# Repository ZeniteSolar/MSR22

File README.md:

# MSR22
Módulo para comunicação serial I2C e USART com duas entradas para leituras analógicas.

Com dois acessos ao barramento I2C e um para USART este módulo foi projetado para os sensores MPU6050 e o módulo GPS Ublox M8N.

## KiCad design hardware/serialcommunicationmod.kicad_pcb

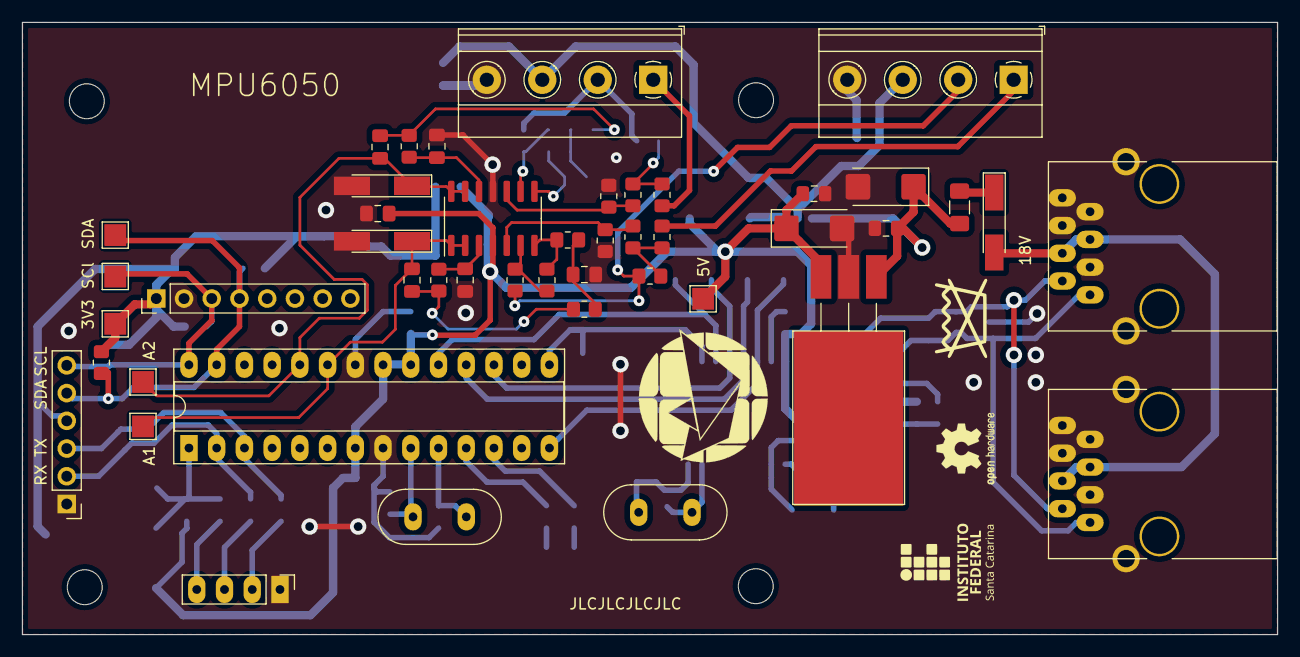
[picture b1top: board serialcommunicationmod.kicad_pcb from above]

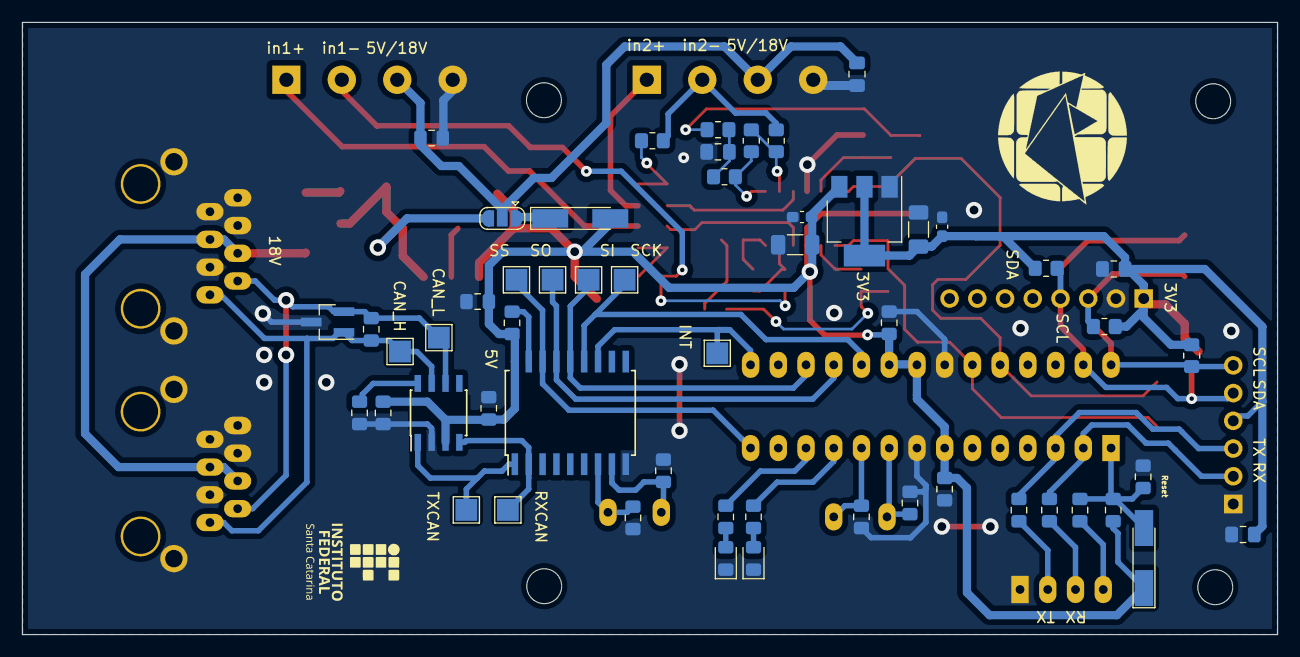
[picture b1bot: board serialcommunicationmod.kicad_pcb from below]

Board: 2 copper layers, 115.0 x 56.1 mm, 110 parts (56 on the bottom side), 55 nets.

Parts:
C4, C5, C6, C7, C8, C9, C374: 100n; C_0805_2012Metric_Pad1.18x1.45mm_HandSolder
C101, C103, C104: 100nF; C_0805_2012Metric_Pad1.18x1.45mm_HandSolder
C102, C201, C202, C205, C401, C402, C405, C406, C502, C503: 100nF; C_0805_2012Metric_Pad1.15x1.40mm_HandSolder
C203, C204, C403, C404: 22pF; C_0805_2012Metric_Pad1.15x1.40mm_HandSolder
C407, C410: 1u; C_1206_3216Metric_Pad1.33x1.80mm_HandSolder
C408, C409: 100n; C_0603_1608Metric_Pad1.08x0.95mm_HandSolder
C501, C504: 1uF; CP_EIA-6032-20_AVX-F_Pad2.25x2.35mm_HandSolder
D2, D3: 4V7; D_MiniMELF_Handsoldering
D101, D401, D501: LL4148; D_MiniMELF_Handsoldering
D201: D_TVS_Dual_AAC; SOT-23_Handsoldering
D402: LED2; LED_0805_2012Metric_Pad1.15x1.40mm_HandSolder
D403: LED1; LED_0805_2012Metric_Pad1.15x1.40mm_HandSolder
F501: 500mA; Fuse_1206_3216Metric_Pad1.42x1.75mm_HandSolder
H101, H102, H103, H104: MountingHole; MountingHole_3.2mm_M3
J101, J102: SENSOR; TerminalBlock_Phoenix_MKDS-1,5-4-5.08_1x04_P5.08mm_Horizont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
J103: Conn_01x08; PinHeader_1x08_P2.54mm_Vertical
J104: Conn_01x06; PinHeader_1x06_P2.54mm_Vertical
J401: USART; PinHeader_1x04_P2.54mm_Vertical
J601, J602: RJ45; RJ45_YH59_01
JP101: jmp; SolderJumper-3_P1.3mm_Open_RoundedPad1.0x1.5mm
LOGO101: Logo_Open_Hardware_Small; OSHW-Logo2_7.3x6mm_SilkScreen
R4, R5, R6, R7, R8, R9, R27, R28, R30, R32, R34, R35, R37, R38, R43, R44, R45, R46: 1k; R_0805_2012Metric_Pad1.20x1.40mm_HandSolder
R101, R102, R103, R104: 10k; R_0805_2012Metric_Pad1.20x1.40mm_HandSolder
R201: 120; R_0805_2012Metric_Pad1.15x1.40mm_HandSolder
R202: 4k7; R_0805_2012Metric_Pad1.15x1.40mm_HandSolder
R203, R401: 10k; R_0805_2012Metric_Pad1.15x1.40mm_HandSolder
R402, R403, R404, R405: 1k; R_0805_2012Metric_Pad1.15x1.40mm_HandSolder
SYM101, SYM102: SYM_Radioactive_Radiation_Small; symbol_logoZenite
SYM103: SYM_Radioactive_Radiation_Small; symbol_naolavar
SYM104, SYM105: SYM_LASER_Small; synbol_logoifsc
TP101: 5V; TestPoint_Pad_2.0x2.0mm
TP102: 3V3; TestPoint_Pad_2.0x2.0mm
TP201: SI; TestPoint_Pad_2.0x2.0mm
TP202: SO; TestPoint_Pad_2.0x2.0mm
TP203: TXCAN; TestPoint_Pad_2.0x2.0mm
TP204: RXCAN; TestPoint_Pad_2.0x2.0mm
TP205: SC; TestPoint_Pad_2.0x2.0mm
TP206: SCK; TestPoint_Pad_2.0x2.0mm
TP207: CAN_H; TestPoint_Pad_2.0x2.0mm
TP208: CAN_L; TestPoint_Pad_2.0x2.0mm
TP209: INT; TestPoint_Pad_2.0x2.0mm
TP210, TP211: TestPoint_Pad_2.0x2.0mm
TP601: SDA; TestPoint_Pad_2.0x2.0mm
TP602: SCL; TestPoint_Pad_2.0x2.0mm
U201: MCP2551-I/SN; SOIC-8_3.9x4.9mm_P1.27mm
U202: MCP2515-xSO; SOIC-18W_7.5x11.6mm_P1.27mm
U301: LM324; SOIC-14_3.9x8.7mm_P1.27mm
U302: DIP-28_W7.62mm_Socket_LongPads
U401: AMS1117-3.3; SOT-223-3_TabPin2
U501: LM7805; TO-220-3_Horizontal_TabDown_SMD
Y201, Y401: 16MHz; Crystal_HC49-U_Vertical

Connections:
+3V3: C103.1, C104.1, C409.2, C410.2, J103.1, J104.4, R101.1, R102.1, R103.1, R104.1, TP102.1, U401.2 (VO)
+5V: C201.1, C202.1, C205.1, C374.1, C401.1, C402.2, C407.2, C408.2, C503.1, C504.1, D101.2 (A), D401.1 (K), R203.1, R401.1, TP101.1, U201.3 (VDD), U202.18 (VDD), U301.4 (V+), U302.7 (VCC), U302.20 (AVCC), U302.21 (AREF), U401.3 (VI), U501.3 (VO)
/CANBUS CONN/CAN_18V: D501.2 (A), J601.4, J601.5, J602.4, J602.5
/CANBUS CONN/CAN_H: D201.1 (A1), J601.1, J602.1, R201.2, TP207.1, U201.7 (CANH)
/CANBUS CONN/CAN_L: D201.2 (A2), J601.2, J602.2, R201.1, TP208.1, U201.6 (CANL)
/CANBUS/RXCAN: TP204.1, U201.4 (RXD), U202.2 (RXCAN)
/CANBUS/TXCAN: TP203.1, U201.1 (TXD), U202.1 (TXCAN)
/MCU/LED1: R405.1, U302.11 (PD5)
/MCU/LED2: R404.1, U302.12 (PD6)
/MCU/MCP_INT: TP209.1, U202.12 (~INT), U302.15 (PB1)
/MCU/MCP_SS: TP205.1, U202.16 (~CS), U302.14 (PB0)
/MCU/RESET: C405.1, C406.2, D401.2 (A), R401.2, U302.1 (~RESET/PC6)
/MCU/analog1: C7.2, D3.1 (K), TP210.1, U301.1, U301.2 (-), U302.23 (PC0)
/MCU/analog2: C6.2, D2.1 (K), TP211.1, U301.13 (-), U301.14, U302.24 (PC1)
/MISO: TP202.1, U202.15 (SO), U302.18 (PB4)
/MOSI: TP201.1, U202.14 (SI), U302.17 (PB3)
/OPAMP/in1+: J102.1, R27.2
/OPAMP/in1-: J102.2, R30.1, R34.1
/OPAMP/in2+: J101.1, R28.2
/OPAMP/in2-: J101.2, R32.1, R37.1
/POWER SUPPLY/+18V_OUT: C501.1, C502.1, F501.2, JP101.3 (B), U501.1 (VI)
/RX: J104.2, R402.1, U302.2 (PD0)
/SCK: TP206.1, U202.13 (SCK), U302.19 (PB5)
/SCL: J103.3, J104.6, R101.2, R103.2, TP602.1, U302.28 (PC5)
/SDA: J103.4, J104.5, R102.2, R104.2, TP601.1, U302.27 (PC4)
/TX: J104.3, R403.1, U302.3 (PD1)
GND: C4.2, C5.2, C8.2, C9.2, C101.2, C102.2, C103.2, C104.2, C201.2, C202.2, C203.2, C204.2, C205.2, C374.2, C401.2, C402.1, C403.2, C404.2, C406.1, C407.1, C408.1, C409.1, C410.1, C501.2, C502.2, C503.2, C504.2, D2.2 (A), D3.2 (A), D201.3 (common), D402.1 (K), D403.1 (K), J101.4, J102.4, J103.2, J104.1, J401.1, J601.3, J601.6, J601.7, J601.8, J601.9 (SH), J602.3, J602.6, J602.7, J602.8, J602.9 (SH), R44.2, R46.2, R202.2, U201.2 (VSS), U202.9 (VSS), U301.11 (V-), U302.8 (GND), U302.22 (GND), U401.1 (GND), U501.2 (GND)
unnamed: C4.1, R4.1, R6.2
unnamed: C5.1, R5.1, R7.2
unnamed: C6.1, R6.1, R8.2
unnamed: C7.1, R7.1, R9.2
unnamed: C8.1, R8.1, U301.12 (+)
unnamed: C9.1, R9.1, U301.3 (+)
unnamed: C101.1, C102.1, J101.3, J102.3, JP101.2 (C)
unnamed: C203.1, U202.7 (OSC2), Y201.1
unnamed: C204.1, U202.8 (OSC1), Y201.2
unnamed: C403.1, U302.10 (XTAL2/PB7), Y401.1
unnamed: C404.1, U302.9 (XTAL1/PB6), Y401.2
unnamed: C405.2, J401.4
unnamed: D101.1 (K), JP101.1 (A)
unnamed: D402.2 (A), R404.2
unnamed: D403.2 (A), R405.2
unnamed: D501.1 (K), F501.1
unnamed: J401.2, R403.2
unnamed: J401.3, R402.2
unnamed: R4.2, R45.2, U301.8
unnamed: R27.1, R30.2, R35.1
unnamed: R28.1, R32.2, R38.1
unnamed: R34.2, R43.1, U301.6 (-)
unnamed: R35.2, R44.1, U301.5 (+)
unnamed: R37.2, R45.1, U301.9 (-)
unnamed: R38.2, R46.1, U301.10 (+)
unnamed: R5.2, R43.2, U301.7
unnamed: R202.1, U201.8 (STBY)
unnamed: R203.2, U202.17 (~RESET)

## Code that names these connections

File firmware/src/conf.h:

/**
 * @file conf.h
 *
 * @defgroup CONF Configurations
 *
 * @brief General configuration of the system.
 *
 */
#ifndef CONF_H
#define CONF_H
#include "../lib/log2.h"

#ifndef F_CPU
#define F_CPU 16000000UL    //define a frequencia do microcontrolador - 16MHz
#endif /* ifndef F_CPU */


// CONFIGURACOES DE COMPILACAO
//#define DEBUG_ON
#define VERBOSE_ON
// #define VERBOSE_ON_CAN_APP
#define VERBOSE_ON_MACHINE
// #define VERBOSE_ON_ADC
#define VERBOSE_ON_INIT
#define VERBOSE_ON_ERROR

// MODULES ACTIVATION
#define USART_ON
#define CAN_ON
//#define CAN_DEPENDENT
#define ADC_ON
#define MACHINE_ON
#define LED_ON
#define WATCHDOG_ON
#define SLEEP_ON
#define PRINT_INFOS

#define CAN_SIGNATURE_SELF                  CAN_SIGNATURE_MSC19_1

#ifdef ADC_ON
// ADC CONFIGURATION
// note that changing ADC_FREQUENCY may cause problems with avg_sum_samples
// #define ADC_8BITS
#define ADC_FREQUENCY                       10000 // 20000
#define ADC_TIMER_PRESCALER                 64
#define ADC_TOP_CTC                         F_CPU/(ADC_TIMER_PRESCALER * 2UL * ADC_FREQUENCY) -1

#if ADC_TOP_CTC >= 256
    #error "Value for ADC timer top is greater than 8 bits"
#elif ADC_TOP_CTC < 2
    #error "Value for ADC timer top is too low, increase the prescaler"
#endif

// #define VSCALE_FACTOR                       10000L  // Scaling to maintain precision, result uint16 for can msg

/** @brief Circular buffer size definitions 
 * Using equal size for adc structures...
 * one could replicate the structure delacartion with different sizes
 * or even, % TODO use dynamic allocation for strucutres 
 */
#define ADC_AVG_SIZE_10                     64
#if (ADC_AVG_SIZE_10 == 0 || (ADC_AVG_SIZE_10 & (ADC_AVG_SIZE_10 - 1)) != 0)
    #error "ADC_AVG_SIZE_10 must be a power of 2!"
#endif
#define cbuf_adc0_SIZE                      ADC_AVG_SIZE_10  /**< Buffer size for ADC0 */
#define cbuf_adc0_SIZE_LOG2                 log2_function(cbuf_adc0_SIZE)   /**< Log2 of buffer size */
#define cbuf_adc1_SIZE                      ADC_AVG_SIZE_10  /**< Buffer size for ADC1 */
#define cbuf_adc1_SIZE_LOG2                 log2_function(cbuf_adc1_SIZE)    /**< Log2 of buffer size */
#endif //ADC_ON



#ifdef MACHINE_ON
// ----> Cbuf used + not a power module ---> no need for even numbers between ADC and Machine frequencies
// no need for clk divider 
#define MACHINE_FREQUENCY                   100           //<! machine timer frequency in Hz
#define MACHINE_TIMER_PRESCALER             1024          //<! machine timer prescaler
#define MACHINE_TOP_CTC                     F_CPU/(MACHINE_TIMER_PRESCALER * 2UL * MACHINE_FREQUENCY) -1
#if MACHINE_TOP_CTC >= 256
    #error "Value for Machine timer top is greater than 8 bits"
#elif MACHINE_TOP_CTC < 2
    #error "Value for Machine timer top is too low, increase the prescaler"
#endif

// The machine frequency may not be superior of ADC_FREQUENCY/ADC_AVG_SIZE_10
#if MACHINE_FREQUENCY > (ADC_FREQUENCY/ADC_AVG_SIZE_10)
    #error "Machine runs faster than the required time to fill the ADC ring buffer"
#endif
#endif // MACHINE_ON

#ifdef LED_ON
#define     LED_PORT                PORTD
#define     LED_PIN                 PIND
#define     LED_DDR                 DDRD
#define     LED1                    PD5
#define     LED2                    PD6
#define     cpl_led(y)              cpl_bit(LED_PORT, y)
#define     set_led(y)              set_bit(LED_PORT, y)
#define     clr_led(y)              clr_bit(LED_PORT, y)
#else
#define     cpl_led()
#define     set_led()
#define     clr_led()
#endif // LED_ON


#ifdef CAN_ON
#define SPI_ON
#define CAN_APP_SEND_STATE_FREQ     10//36000     //<! state msg frequency in Hz
#define CAN_APP_SEND_ADC_FREQ       50//6000      //<! adc msg frequency in Hz
#if MACHINE_FREQUENCY % CAN_APP_SEND_STATE_FREQ != 0
    #warning "CAN_APP_SEND_STATE_FREQ doesn't have a multiple equal to MACHINE_FREQUENCY, this frequency will be truncated"
#endif

#if MACHINE_FREQUENCY % CAN_APP_SEND_ADC_FREQ != 0
    #warning "CAN_APP_SEND_ADC_FREQ doesn't have a multiple equal to MACHINE_FREQUENCY, this frequency will be truncated"
#endif

// CANBUS DEFINITONS
// ----------------------------------------------------------------------------
/* Global settings for building the can-lib and application program.
 *
 * The following two #defines must be set identically for the can-lib and
 * your application program. They control the underlying CAN struct. If the
 * settings disagree, the underlying CAN struct will be broken, with
 * unpredictable results.
 * If can.h detects that any of the #defines is not defined, it will set them
 * to the default values shown here, so it is in your own interest to have a
 * consistent setting. Ommiting the #defines in both can-lib and application
 * program will apply the defaults in a consistent way too.
 *
 * Select if you want to use 29 bit identifiers.
 */
#define	SUPPORT_EXTENDED_CANID	0

/* Select if you want to use timestamps.
 * Timestamps are sourced from a register internal to the AT90CAN.
 * Selecting them on any other controller will have no effect, they will
 * be 0 all the time.
 */
#define	SUPPORT_TIMESTAMPS		0
#endif // CAN_ON

#endif /* ifndef CONF_H */

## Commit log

2022-07-01 hardware: silkscreen updated with JLC. Finished.
2022-09-25 Copy firmware from MVC19, removed ui.*
2022-09-25 remove UI
2022-09-25 Remove oled-display
2022-09-25 Added gps files
2025-03-19 commit inicial do modo voltimetro
2025-03-23 implement log2 function aside from macro
2025-03-23 add missing prototypes
2025-03-23 using macros for led_clk_div, code cleanup
2025-03-23 remove linearization that was inside can_app ???
2025-03-23 thorough adc init, corrected channels switch case, improved macros
2025-03-23 Compiler safeguard for macros of ADC and machine timers
2025-03-31 Working macros, beginning linearization
2025-03-31 Code cleanup
2025-04-04 begin linearization
2025-04-04 fix adc prescaler
2025-04-04 Reminder to redefine maximum values
2025-06-03 Linearization coeffs
2025-06-03 using new adc functions, voltage limites, and led frequencies
2025-06-03 New adc functions, pretending to be MSC19 1 and 2
2025-06-03 State msg is still CAN...SELF, pretend to be MSC19_1
2025-06-03 linearization files
2025-06-03 minor changes to LED logic
2025-06-03 WARN against non-integer can_app clk_div frequencies
2025-06-08 remove unused code,organization
2025-06-08 remove unused machine_clk_div from ISR
2025-06-14 ADC msg: all 7 bytes present, not all implemented
